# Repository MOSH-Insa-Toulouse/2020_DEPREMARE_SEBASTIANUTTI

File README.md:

# 2020_DEPREMARE_SEBASTIANUTTI
## MOSH - Smart Sensor

Au cours de projet MOSH, nous avons réalisé de A à Z un capteur intelligent. Ce repository à pour but de partager les différentes étapes de la réalisation de ce sensor.
Il contient : 
- La datasheet du capteur réalisé
- Le schéma LtSpice de validation du circuit de traitement du capteur
- Les schémas électronique et du PCB réalisé avec KiCad
- Le code arduino pour envoyer les données sur TTN
- Un flow Node Red pour recevoir ces données

Le capteur à été réalisé en salle blanche puis caractérisé pour en produire la datasheet. Dans un second temps nous avons réalisé un schéma électronique afin de mesurer le gaz capté par le capteur en suivant la datasheet. Ce schéma se trouve dans le dossier ltspice. Il a ensuite été mis en application sur KiCad

## KiCad - Du prototype à l'industrialisation

### Schéma electronique

Après avoir validé le schéma sur LtSpice, nous l'avons modélisé sur KiCad. Pour cela nous avons du créer les composants inexistants dans les librairies initiales. Voici ci-dessous le schéma global du système :

*Fig.1: Schématique dessinée sur KiCad*

### Shield Arduino Uno

Le shield créé à pour but l'industrialisation du système, il comporte les trou pour y souder notre capteur de gaz, le circuit de traitement du signal schématisé ci-dessus ainsi qu'un bouton pour activer un capteur industriel en cas de défaillance du capteur à nano particules et une LED qui s'allume dans ce cas. un espace est libre sur la carte afin de pouvoir y brancher le module LoRa pour envoyer les données sur TTN.

*Fig.2: Vue de dessus en 3D du PCB*

Pour plus de clarté, voici la vue schématique :

*Fig.3: Schéma du PCB dessiné sur KiCad*

## Utilisation avec microcontrolleur

Le code Arduino fourni permet de récupérer les données du capteur directement depuis la shield KiCad et de l'envoyer sur The Things Network. Attention cependant, nous n'avons pas pu tester la shield en condition réelle, il est donc possible que des problèmes d'intégration surviennent.

*Fig.4: Montage prototype avec mesure de consomation*

Comme présenté sur la figure ci-dessus, nous avons mesuré la consomation du système pour voir où économiser de l'énergie. Nous nous sommes rendu compte que la résistance chauffante du capteur était responsable de la consomation du système et que le reste était négligeable devant celle-ci. Nous proposons donc comme améioration une utilisation non pas encontinue mais par exemple une mesure toutes les minutes (bien sûr l'interval serait à adapter en fonction du cas d'utilisation).

*Fig.5: Puce RN2483 soudée sur une carte untégrable sur la Shield KiCad*

## Utilisation des données

Une fois sur TTN, nous avons utilisé un serveur gratuit Node Red pour visualiser les données et en avons fait un graph. Nous avon voulu intégrer cette vue à una application mobile développée grace au MIT App Inventor mais le serveur Node Red ne permettant l'accès qu'à une socket particulière nous à empêché de mener le projet à bout.

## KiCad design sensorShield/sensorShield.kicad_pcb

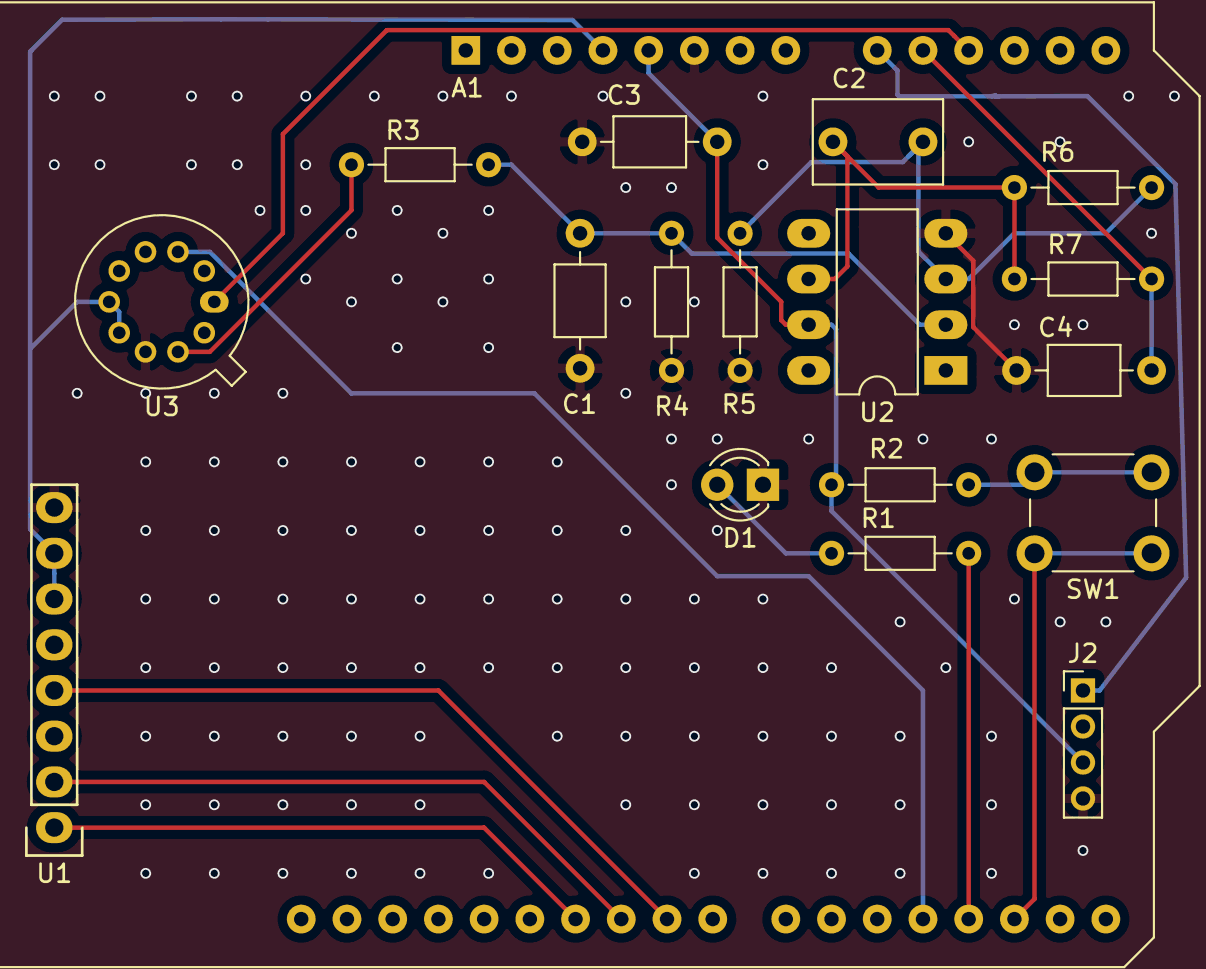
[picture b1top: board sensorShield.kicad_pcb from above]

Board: 2 copper layers, 18 parts (0 on the bottom side), 18 nets.

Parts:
A1: Arduino_UNO_R3
C1, C3, C4: 100n; C_Axial_L3.8mm_D2.6mm_P7.50mm_Horizontal
C2: 1µ; C_Rect_L7.0mm_W4.5mm_P5.00mm
D1: LED; LED_D3.0mm
J2: GrooveGasSensor; PinHeader_1x04_P2.00mm_Vertical
R1, R3: 10k; R_Axial_DIN0204_L3.6mm_D1.6mm_P7.62mm_Horizontal
R2: 330; R_Axial_DIN0204_L3.6mm_D1.6mm_P7.62mm_Horizontal
R4, R6: 100k; R_Axial_DIN0204_L3.6mm_D1.6mm_P7.62mm_Horizontal
R5, R7: 1k; R_Axial_DIN0204_L3.6mm_D1.6mm_P7.62mm_Horizontal
SW1: SW_Push; SW_PUSH_6mm
U1: RN2483A; Socket_Strip_Arduino_1x08
U2: LTC1050; DIP-8_W7.62mm_LongPads
U3: GazSensor; TO-5-10

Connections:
+3V3: A1.4, U1.6, U1.7, U3.4, U3.5
+5V: A1.5, C3.1, J2.3, R1.2, U2.7
A0: A1.9, J2.1
A1: A1.10, C4.1, R7.1
CapTemp: A1.11, U3.10
D2: A1.17, SW1.1
D3: A1.18, R2.2
GND: A1.6, C1.2, C3.2, C4.2, D1.1, J2.4, R4.1, R5.1, U1.8, U2.4, U3.3
unnamed: C1.1, R3.1, R4.2, U2.2
unnamed: C2.1, R5.2, R6.2, U2.3
unnamed: C2.2, R6.1, R7.2, U2.6
unnamed: D1.2, R2.1
unnamed: R1.1, SW1.2
RChauff: A1.19, U3.8
RST: A1.24, U1.4
Rsensor: R3.2, U3.2
Rx: A1.25, U1.2
Tx: A1.26, U1.1

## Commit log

2020-12-02 KiCad shieldMosh Project initialized
2020-12-04 Add arduino code.(periodic TTN upload)
2020-12-04 Add node-red flow.(TTN read, graph display, fake gaz calculation.)
2020-12-09 Add ltspice similation circuit.
2020-12-09 Update UNO template.
2020-12-09 analog elec schematized
2020-12-09 sensor schematized
2020-12-09 sensor schematized v2
2021-01-17 KiCad push
2021-01-17 Datasheet added
2021-01-17 Cleaning and README
